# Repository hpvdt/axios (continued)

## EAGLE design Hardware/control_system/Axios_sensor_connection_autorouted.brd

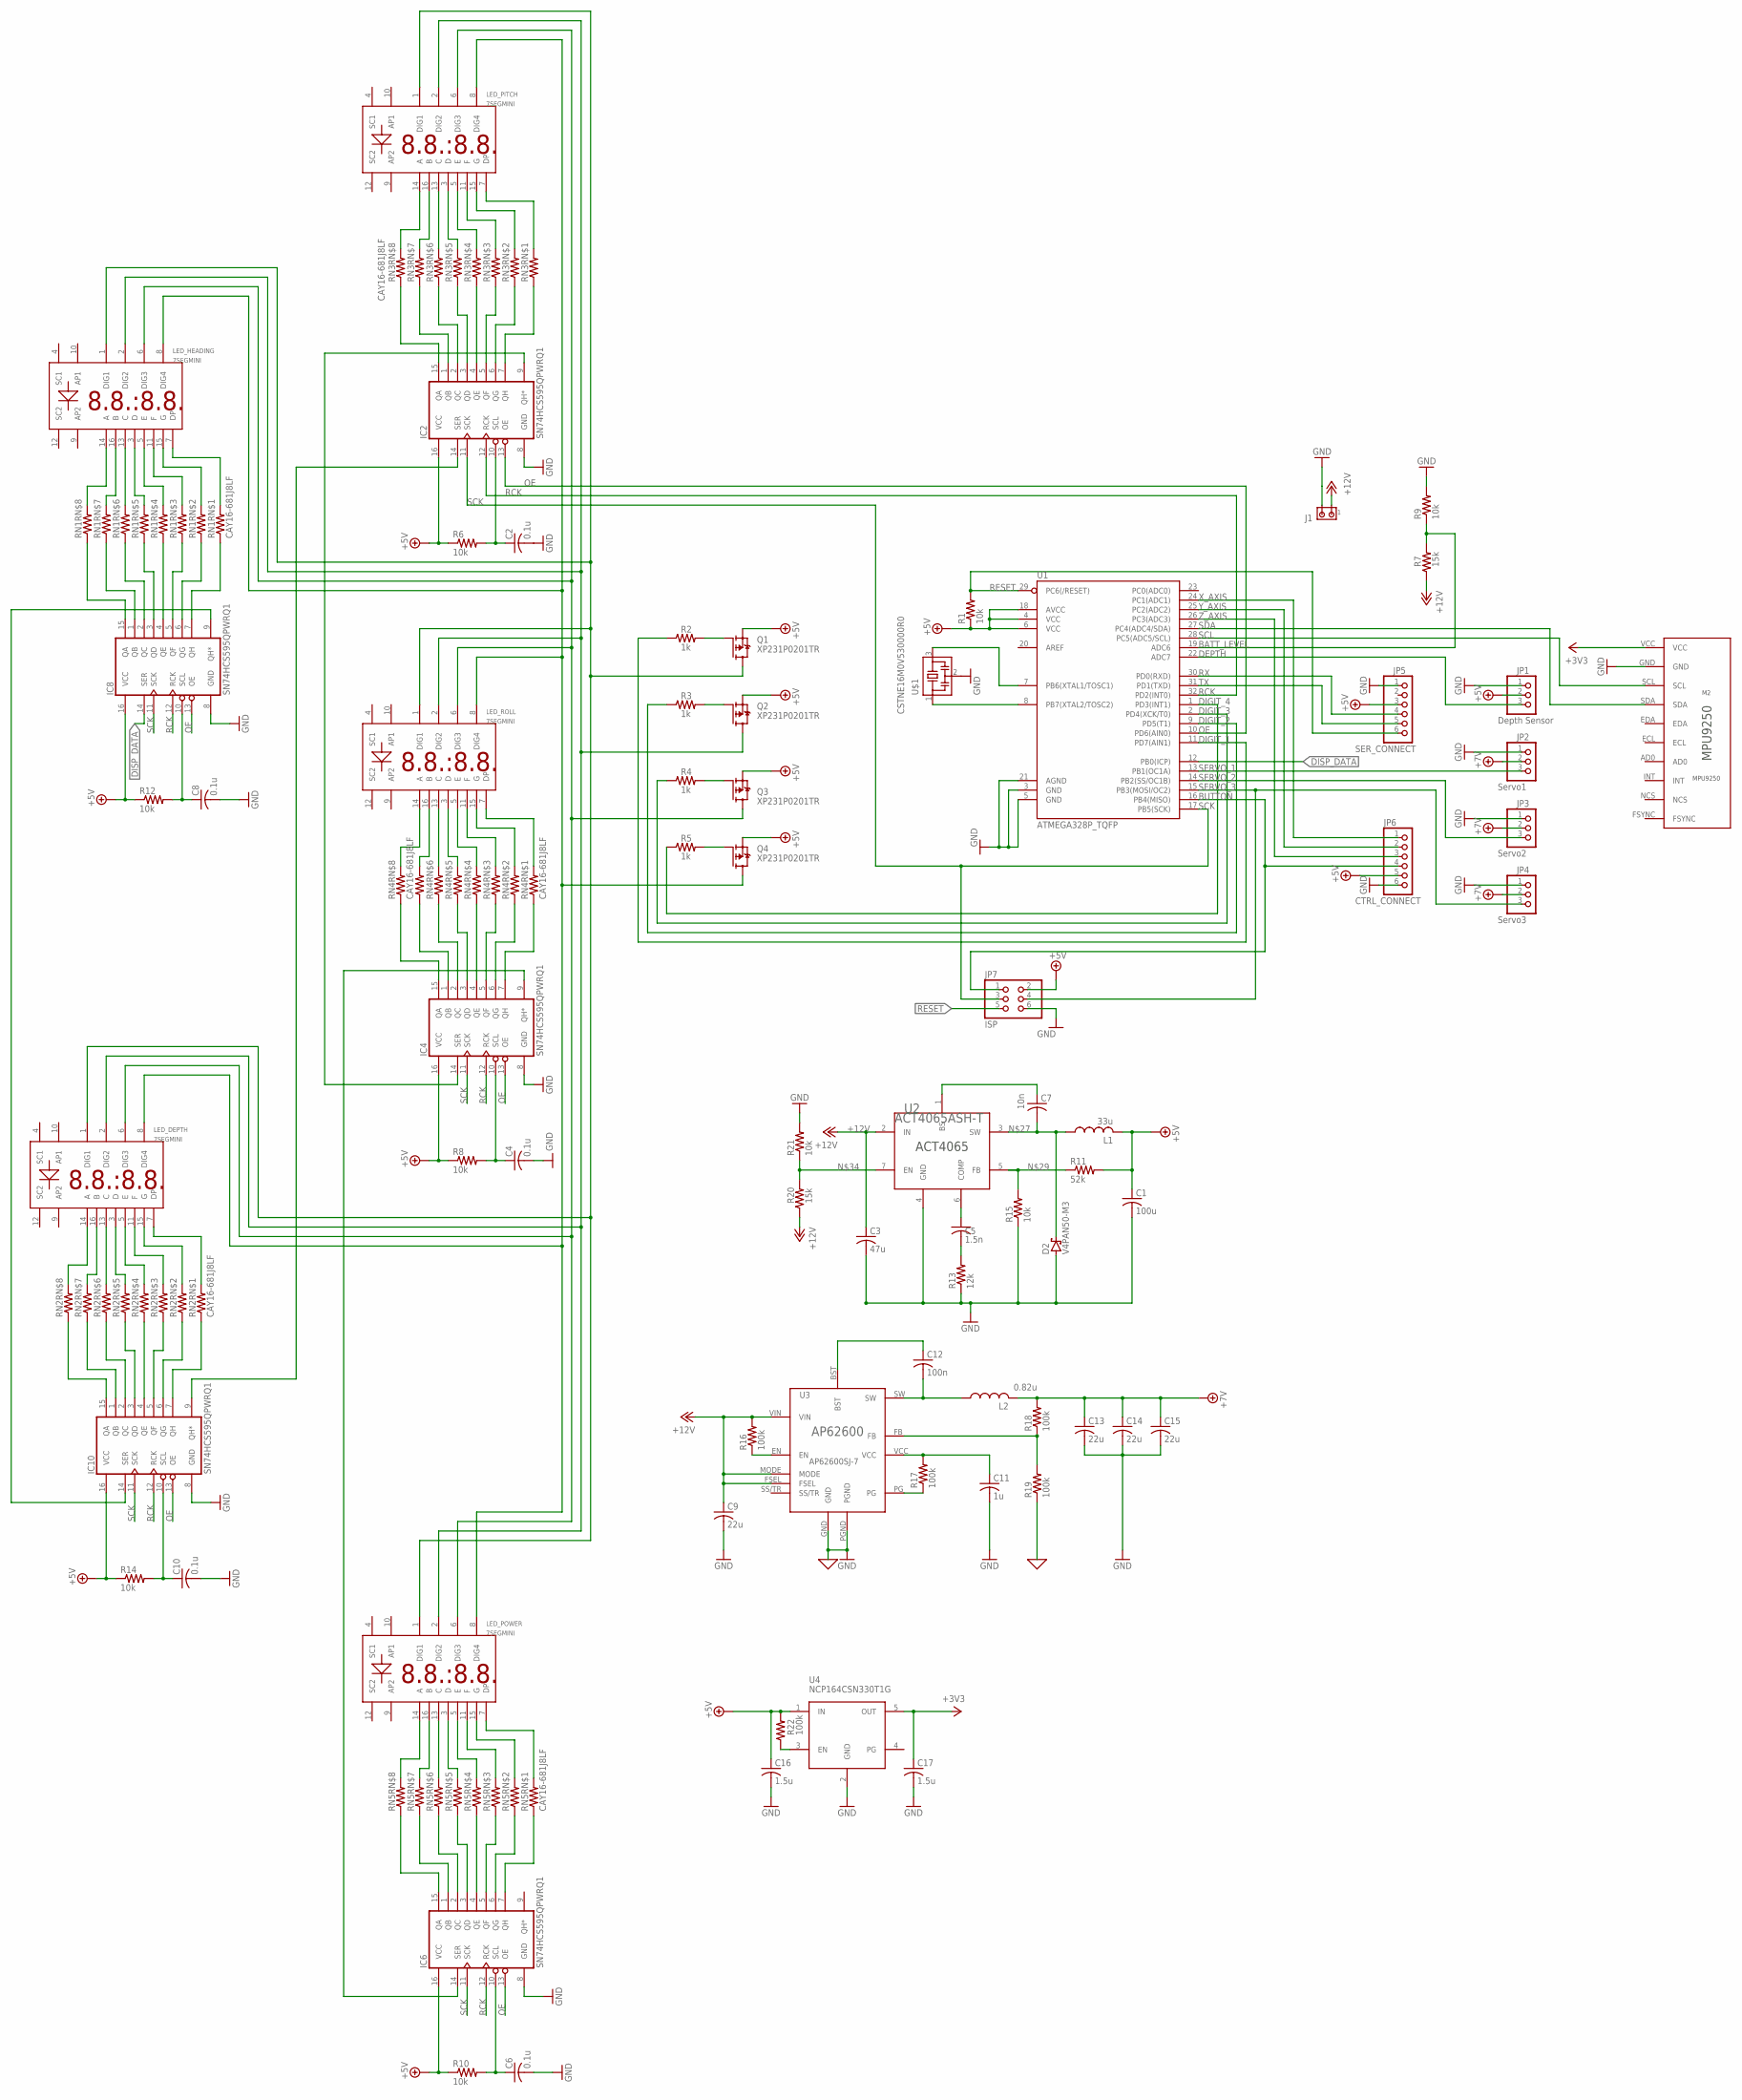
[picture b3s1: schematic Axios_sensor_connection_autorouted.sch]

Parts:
C1: 100u; C0603
C2, C4, C6, C8, C10: 0.1u; C0603
C3: 47u; C0603
C5: 1.5n; C0603
C7: 10n; C0603
C9, C13, C14, C15: 22u; C0603
C11: 1u; C0603
C12: 100n; C0603
C16, C17: 1.5u; C0603
D2: V4PAN50-M3; SMPA
IC2, IC4, IC6, IC8, IC10: SN74HCS595QPWRQ1; TSSOP16
J1: MTA02-156; 1X2MTA
JP1: Depth Sensor; 1X03
JP2: Servo1; 1X03
JP3: Servo2; 1X03
JP4: Servo3; 1X03
JP5: SER_CONNECT; 1X06
JP6: CTRL_CONNECT; 1X06
JP7: ISP; 2X03
L1: 33u; SRN1060-330M
L2: 0.82u; ECS-MPIL0630-R82MC
LED_DEPTH: 7SEGMINI
LED_HEADING: 7SEGMINI
LED_PITCH: 7SEGMINI
LED_POWER: 7SEGMINI
LED_ROLL: 7SEGMINI
M2: MPU9250
Q1, Q2, Q3, Q4: XP231P0201TR; SOT23
R1, R6, R8, R9, R10, R12, R14, R15, R21: 10k; R0603
R2, R3, R4, R5: 1k; R0603
R7, R20: 15k; R0603
R11: 52k; R0603
R13: 12k; R0603
R16, R17, R18, R19, R22: 100k; R0603
RN1, RN2, RN3, RN4, RN5: CAY16-681J8LF
U1: ATMEGA328P_TQFP; TQFP32-08
U2: ACT4065ASH-T; SO8
U3: AP62600SJ-7; V-QFN2030-12
U4: NCP164CSN330T1G; TSOP-5
U$1: CSTNE16M0V530000R0; CSTCR6M

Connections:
0: R19.1, U3.GND, U3.PGND
+3V3: C17.1, M2.VCC, U4.5 (OUT)
+5V: C1.1, C16.1, IC2.16 (VCC), IC4.16 (VCC), IC6.16 (VCC), IC8.16 (VCC), IC10.16 (VCC), JP1.2, JP2.2, JP3.2, JP4.2, JP5.3, JP6.5, JP7.2, L1.P$2 (2), Q1.2 (S), Q2.2 (S), Q3.2 (S), Q4.2 (S), R6.1, R8.1, R10.1, R11.2, R12.1, R14.1, R22.2, U4.1 (IN)
+7V: C13.1, C14.1, C15.1, L2.P$2 (2), R18.2
+12V: C3.1, C9.1, J1.1, R7.1, R16.2, R20.1, U2.2 (IN), U3.FSEL, U3.MODE, U3.VIN
BATT_LEVEL: R7.2, R9.1, U1.19 (ADC6)
BUTTON: JP6.4, JP7.1, U1.16 (PB4(MISO))
DEPTH: JP1.3, U1.22 (ADC7)
DIGIT_1: R2.1, U1.11 (PD7(AIN1))
DIGIT_2: R3.1, U1.9 (PD5(T1))
DIGIT_3: R4.1, U1.2 (PD4(XCK/T0))
DIGIT_4: R5.1, U1.1 (PD3(INT1))
DISP_DATA: IC8.14 (SER), U1.12 (PB0(ICP))
GND: C1.2, C2.2, C3.2, C4.2, C6.2, C8.2, C9.2, C10.2, C11.2, C13.2, C14.2, C15.2, C16.2, C17.2, D2.A, IC2.8 (GND), IC4.8 (GND), IC6.8 (GND), IC8.8 (GND), IC10.8 (GND), JP1.1, JP2.1, JP3.1, JP4.1, JP5.1, JP6.6, JP7.6, M2.GND, R9.2, R13.1, R15.1, R21.2, U1.3 (GND), U1.5 (GND), U1.21 (AGND), U2.4 (GND), U4.2 (GND), U$1.2
GND1: R17.1, U3.PG
GND2: R16.1, U3.EN
unnamed: R1.1, U1.4 (VCC), U1.6 (VCC), U1.18 (AVCC)
unnamed: IC8.9 (QH*), IC10.14 (SER)
unnamed: U1.8 (PB7(XTAL2/TOSC2)), U$1.1
unnamed: U1.7 (PB6(XTAL1/TOSC1)), U$1.3
unnamed: C7.1, U2.1 (BS)
unnamed: Q1.1 (G), R2.2
unnamed: Q2.1 (G), R3.2
unnamed: Q3.1 (G), R4.2
unnamed: Q4.1 (G), R5.2
unnamed: C7.2, D2.C, L1.P$1 (1), U2.3 (SW)
unnamed: R11.1, R15.2, U2.5 (FB)
unnamed: R22.1, U4.3 (EN)
unnamed: C5.2, R13.2
unnamed: R20.2, R21.1, U2.7 (EN)
unnamed: C5.1, U2.6 (COMP)
unnamed: C11.1, R17.2, U3.VCC
unnamed: C12.2, L2.P$1 (1), U3.SW
unnamed: R18.1, R19.2, U3.FB
unnamed: LED_PITCH.14 (A), RN3.9 (2)
unnamed: LED_PITCH.16 (B), RN3.10 (2)
unnamed: LED_PITCH.13 (C), RN3.11 (2)
unnamed: LED_PITCH.3 (D), RN3.12 (2)
unnamed: LED_PITCH.5 (E), RN3.13 (2)
unnamed: LED_PITCH.11 (F), RN3.14 (2)
unnamed: LED_PITCH.15 (G), RN3.15 (2)
unnamed: LED_PITCH.7 (DP), RN3.16 (2)
unnamed: IC2.15 (QA), RN3.8 (1)
unnamed: IC2.1 (QB), RN3.7 (1)
unnamed: IC2.2 (QC), RN3.6 (1)
unnamed: IC2.3 (QD), RN3.5 (1)
unnamed: IC2.4 (QE), RN3.4 (1)
unnamed: IC2.5 (QF), RN3.3 (1)
unnamed: IC2.6 (QG), RN3.2 (1)
unnamed: IC2.7 (QH), RN3.1
unnamed: C2.1, IC2.10 (SCL), R6.2
unnamed: C12.1, U3.BST
unnamed: IC2.14 (SER), IC10.9 (QH*)
unnamed: LED_ROLL.14 (A), RN4.9 (2)
unnamed: LED_ROLL.16 (B), RN4.10 (2)
unnamed: LED_ROLL.13 (C), RN4.11 (2)
unnamed: LED_ROLL.3 (D), RN4.12 (2)
unnamed: LED_ROLL.5 (E), RN4.13 (2)
unnamed: LED_ROLL.11 (F), RN4.14 (2)
unnamed: LED_ROLL.15 (G), RN4.15 (2)
unnamed: LED_ROLL.7 (DP), RN4.16 (2)
unnamed: IC4.15 (QA), RN4.8 (1)
unnamed: IC4.1 (QB), RN4.7 (1)
unnamed: IC4.2 (QC), RN4.6 (1)
unnamed: IC4.3 (QD), RN4.5 (1)
unnamed: IC4.4 (QE), RN4.4 (1)
unnamed: IC4.5 (QF), RN4.3 (1)
unnamed: IC4.6 (QG), RN4.2 (1)
unnamed: IC4.7 (QH), RN4.1
unnamed: C4.1, IC4.10 (SCL), R8.2
unnamed: IC2.9 (QH*), IC4.14 (SER)
unnamed: LED_POWER.14 (A), RN5.9 (2)
unnamed: LED_POWER.16 (B), RN5.10 (2)
unnamed: LED_POWER.13 (C), RN5.11 (2)
unnamed: LED_POWER.3 (D), RN5.12 (2)
unnamed: LED_POWER.5 (E), RN5.13 (2)
unnamed: LED_POWER.11 (F), RN5.14 (2)
unnamed: LED_POWER.15 (G), RN5.15 (2)
unnamed: LED_POWER.7 (DP), RN5.16 (2)
unnamed: IC6.15 (QA), RN5.8 (1)
unnamed: IC6.1 (QB), RN5.7 (1)
unnamed: IC6.2 (QC), RN5.6 (1)
unnamed: IC6.3 (QD), RN5.5 (1)
unnamed: IC6.4 (QE), RN5.4 (1)
unnamed: IC6.5 (QF), RN5.3 (1)
unnamed: IC6.6 (QG), RN5.2 (1)
unnamed: IC6.7 (QH), RN5.1
unnamed: C6.1, IC6.10 (SCL), R10.2
unnamed: IC4.9 (QH*), IC6.14 (SER)
unnamed: LED_HEADING.14 (A), RN1.9 (2)
unnamed: LED_HEADING.16 (B), RN1.10 (2)
unnamed: LED_HEADING.13 (C), RN1.11 (2)
unnamed: LED_HEADING.3 (D), RN1.12 (2)
unnamed: LED_HEADING.5 (E), RN1.13 (2)
unnamed: LED_HEADING.11 (F), RN1.14 (2)
unnamed: LED_HEADING.15 (G), RN1.15 (2)
unnamed: LED_HEADING.7 (DP), RN1.16 (2)
unnamed: IC8.15 (QA), RN1.8 (1)
unnamed: IC8.1 (QB), RN1.7 (1)
unnamed: IC8.2 (QC), RN1.6 (1)
unnamed: IC8.3 (QD), RN1.5 (1)
unnamed: IC8.4 (QE), RN1.4 (1)
unnamed: IC8.5 (QF), RN1.3 (1)
unnamed: IC8.6 (QG), RN1.2 (1)
unnamed: IC8.7 (QH), RN1.1
unnamed: C8.1, IC8.10 (SCL), R12.2
unnamed: LED_DEPTH.1 (DIG1), LED_HEADING.1 (DIG1), LED_PITCH.1 (DIG1), LED_POWER.1 (DIG1), LED_ROLL.1 (DIG1), Q1.3 (D)
unnamed: LED_DEPTH.2 (DIG2), LED_HEADING.2 (DIG2), LED_PITCH.2 (DIG2), LED_POWER.2 (DIG2), LED_ROLL.2 (DIG2), Q2.3 (D)
unnamed: LED_DEPTH.6 (DIG3), LED_HEADING.6 (DIG3), LED_PITCH.6 (DIG3), LED_POWER.6 (DIG3), LED_ROLL.6 (DIG3), Q3.3 (D)
unnamed: LED_DEPTH.8 (DIG4), LED_HEADING.8 (DIG4), LED_PITCH.8 (DIG4), LED_POWER.8 (DIG4), LED_ROLL.8 (DIG4), Q4.3 (D)
unnamed: LED_DEPTH.14 (A), RN2.9 (2)
unnamed: LED_DEPTH.16 (B), RN2.10 (2)
unnamed: LED_DEPTH.13 (C), RN2.11 (2)
unnamed: LED_DEPTH.3 (D), RN2.12 (2)
unnamed: LED_DEPTH.5 (E), RN2.13 (2)
unnamed: LED_DEPTH.11 (F), RN2.14 (2)
unnamed: LED_DEPTH.15 (G), RN2.15 (2)
unnamed: LED_DEPTH.7 (DP), RN2.16 (2)
unnamed: IC10.15 (QA), RN2.8 (1)
unnamed: IC10.1 (QB), RN2.7 (1)
unnamed: IC10.2 (QC), RN2.6 (1)
unnamed: IC10.3 (QD), RN2.5 (1)
unnamed: IC10.4 (QE), RN2.4 (1)
unnamed: IC10.5 (QF), RN2.3 (1)
unnamed: IC10.6 (QG), RN2.2 (1)
unnamed: IC10.7 (QH), RN2.1
unnamed: C10.1, IC10.10 (SCL), R14.2
OE: IC2.13 (OE), IC4.13 (OE), IC6.13 (OE), IC8.13 (OE), IC10.13 (OE), U1.10 (PD6(AIN0))
RCK: IC2.12 (RCK), IC4.12 (RCK), IC6.12 (RCK), IC8.12 (RCK), IC10.12 (RCK), U1.32 (PD2(INT0))
RESET: JP5.6, JP7.5, R1.2, U1.29 (PC6(/RESET))
RX: JP5.4, U1.30 (PD0(RXD))
SCK: IC2.11 (SCK), IC4.11 (SCK), IC6.11 (SCK), IC8.11 (SCK), IC10.11 (SCK), JP7.3, U1.17 (PB5(SCK))
SCL: M2.SCL, U1.28 (PC5(ADC5/SCL))
SDA: M2.SDA, U1.27 (PC4(ADC4/SDA))
SERVO_1: JP2.3, U1.13 (PB1(OC1A))
SERVO_2: JP3.3, U1.14 (PB2(SS/OC1B))
SERVO_3: JP4.3, JP7.4, U1.15 (PB3(MOSI/OC2))
TX: JP5.5, U1.31 (PD1(TXD))
X_AXIS: JP6.1, U1.24 (PC1(ADC1))
Y_AXIS: JP6.2, U1.25 (PC2(ADC2))
Z_AXIS: JP6.3, U1.26 (PC3(ADC3))

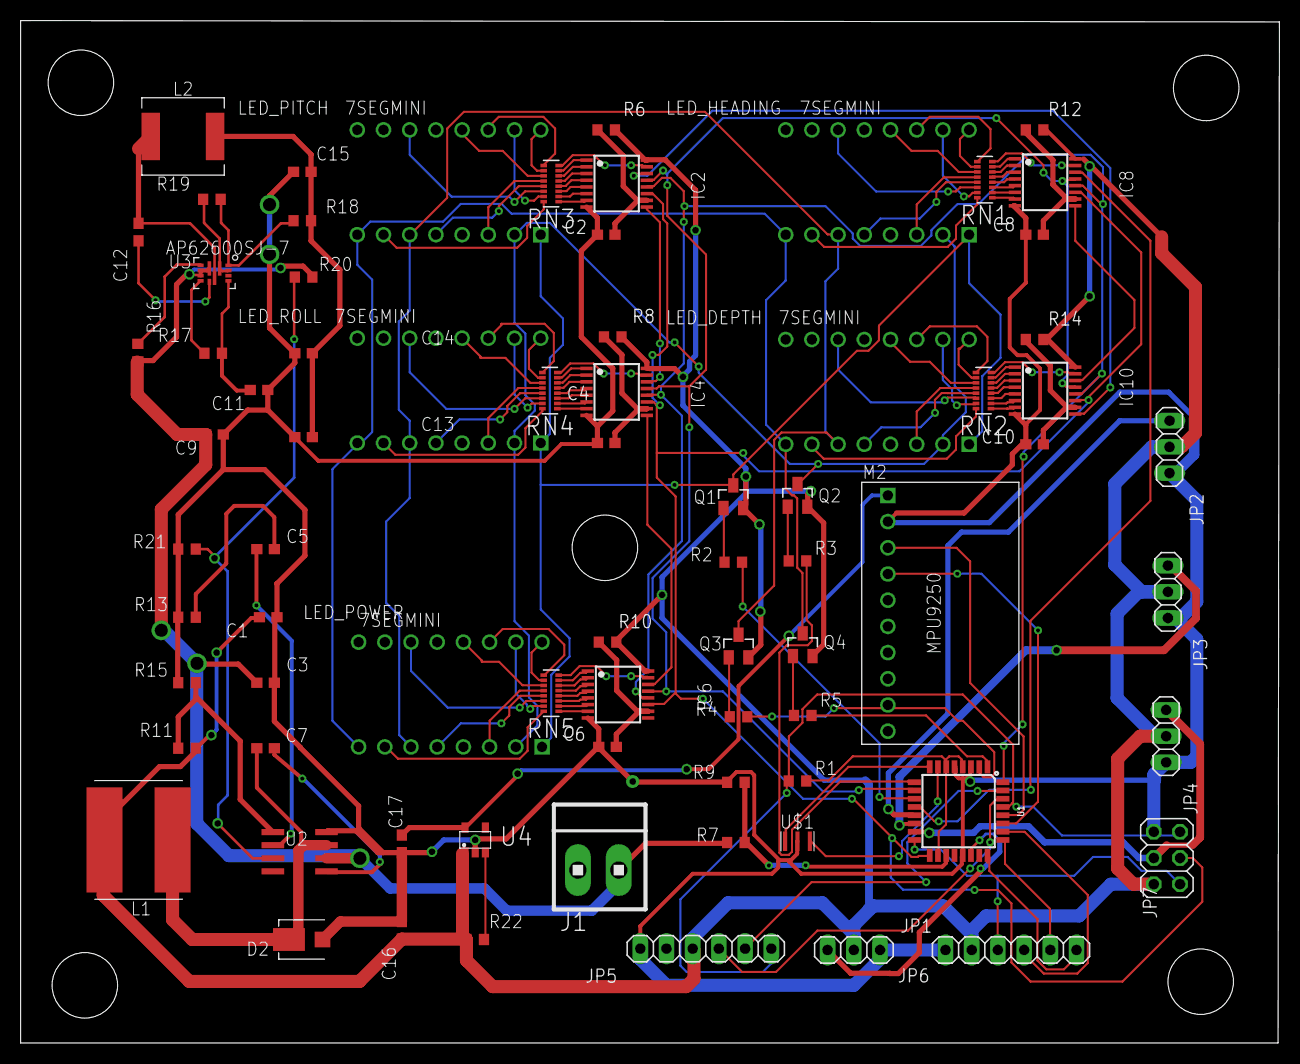
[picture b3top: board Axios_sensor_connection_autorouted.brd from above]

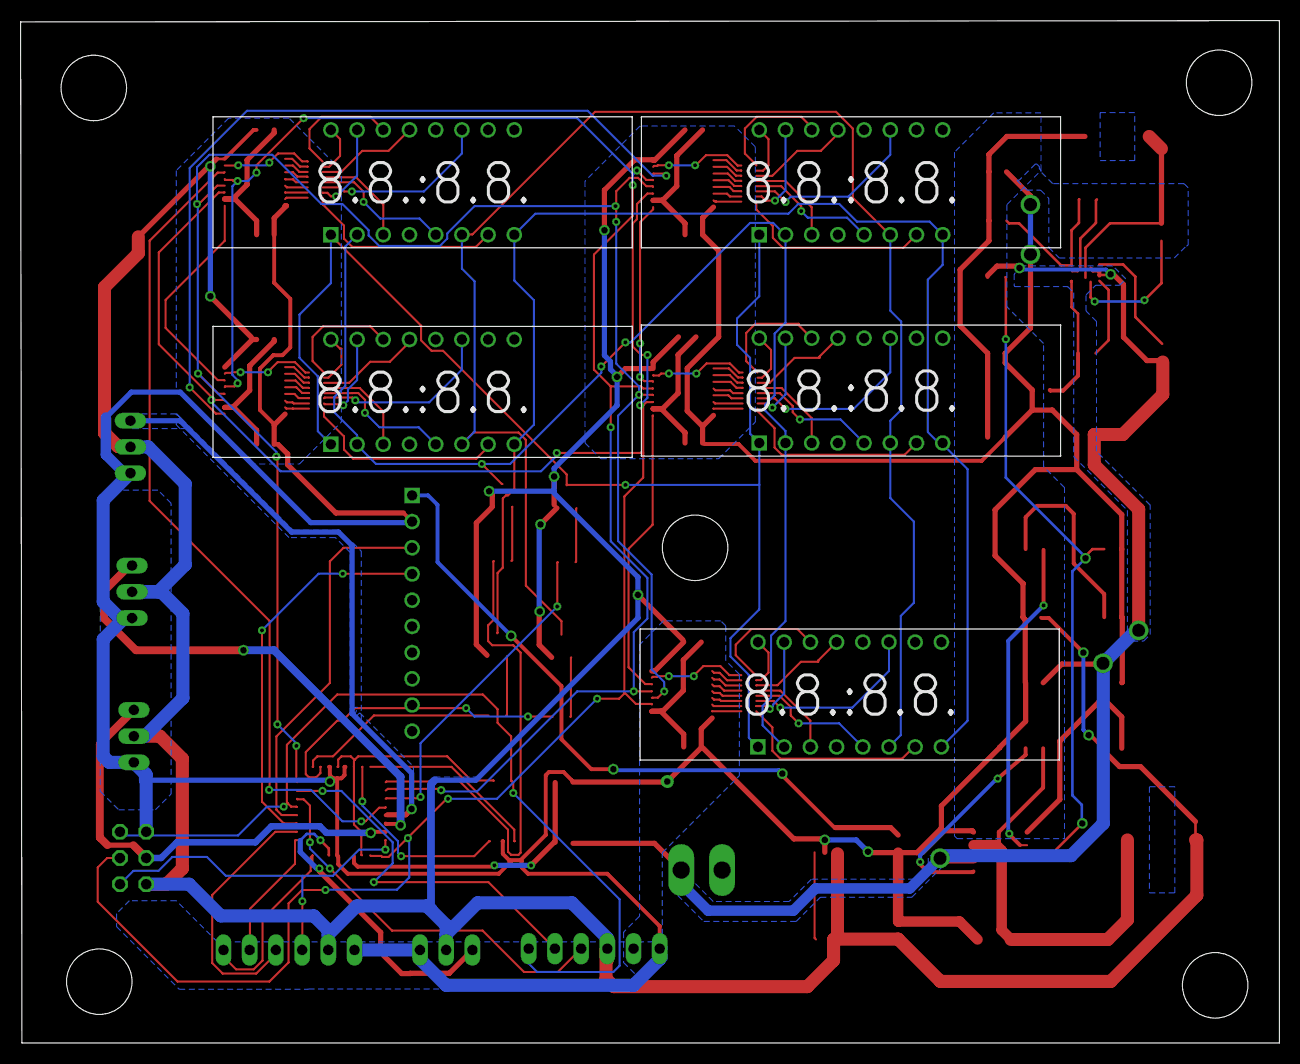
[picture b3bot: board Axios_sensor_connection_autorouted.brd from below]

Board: 2 copper layers, 122.0 x 99.1 mm, 75 parts (5 on the bottom side), 141 nets.

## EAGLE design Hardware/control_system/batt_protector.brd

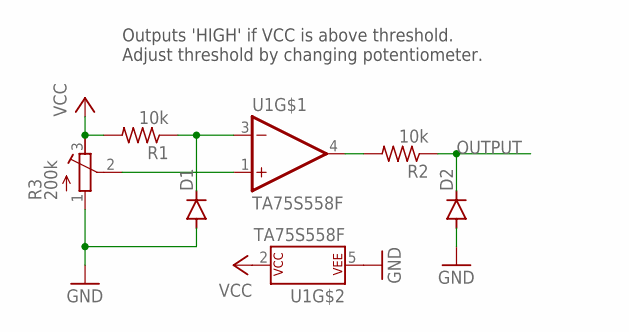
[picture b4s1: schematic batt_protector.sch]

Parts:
D1, D2: DIODE-SOD323-R; SOD323-R
R1, R2: 10k; R0603
R3: 200k; RTRIM64P
U1: TA75S558F; SOTFL95P275X130-5N

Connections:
GND: D1.A, D2.A, R3.1 (A), U1.5 (P$V-)
INPUT: R3.2 (S), U1.1 (+IN)
unnamed: R2.2, U1.4 (OUT)
OUTPUT: D2.C, R2.1
REFV: D1.C, R1.1, U1.3 (-IN)
VCC: R1.2, R3.3 (E), U1.2 (P$V+)

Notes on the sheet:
Outputs 'HIGH' if VCC is above threshold. Adjust threshold by changing potentiometer.

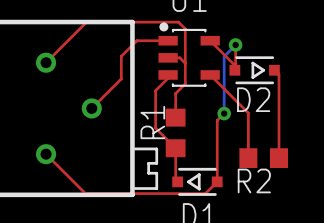
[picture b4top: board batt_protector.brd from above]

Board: 2 copper layers, 6 parts (0 on the bottom side), 6 nets.

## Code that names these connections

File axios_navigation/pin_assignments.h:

#ifndef PIN_HEADER
#define PIN_HEADER
/* Pin Allocations

    Control Related:
    A1 - "X" axis - Right Horizontal
    A2 - "Y" axis - Right Vertical
    A3 - "Z" axis - Left Horizontal
    D12 - PB4 - Left pressed

    D9 - PB1 - Servo 1
    D10 - PB2 - Servo 2
    D11 - PB3 - Servo 3

    Sensing:
    A6 - Battery Level
    A7 - Depth

    Display Pins:
    PD3 - Digit 4
    PD4 - Digit 3
    PD5 - Digit 2
    PD7 - Digit 1

    PD2 - Output clock
    PD6 - Output enable
    PB0 - Display data
    PB5 - Display clock
    
    Displays in order: POWER (0), ROLL, PITCH, DEPTH, HEADING (4)
*/

const byte leftHorizontalPin = A3;
const byte rightHorizontalPin = A1;
const byte rightVerticalPin = A2;
const byte leftPressedPin = 12;

const byte servoPins[] = {9,10, 11}; // Servos: top, left, right

const byte batteryPin = A6;
const byte depthPin = A7;

#endif

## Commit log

2020-04-20 Project Guidelines
2021-05-13 Initial commit of current code
    Rebreather code is basically done. Navigation code needs some work especially with the orientation data.
2021-06-06 Uploaded hardware related files
    The boards were designed using EAGLE
2022-04-01 Uploaded tested CO2 code
    Tested and verified CO2 code for Axios
2022-04-01 Fixing CO2 sensor span
    CO2 sensor was labelled with a span of 5000ppm, not 2000
2022-04-01 Modified oxygen reading code against noise
    Needed to make the system read uninterrupted since the displays getting updated produces significant noise.
2022-10-20 Updated readme following retirement of project
2022-10-20 Fixed image with branch name change
2022-10-20 Fixed some spelling and photo reference
